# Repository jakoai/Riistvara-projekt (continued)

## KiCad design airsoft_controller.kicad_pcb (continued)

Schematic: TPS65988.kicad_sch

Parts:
C88, C90, C97: 4.7uF; C_0603_1608Metric_Pad1.08x0.95mm_HandSolder
C89, C98: 10uF; C_0805_2012Metric_Pad1.18x1.45mm_HandSolder
C91, C94, C100, C106: 1uF; C_0603_1608Metric_Pad1.08x0.95mm_HandSolder
C92, C93, C95, C96: 220pF; C_0603_1608Metric_Pad1.08x0.95mm_HandSolder
C99, C105: 0.1uF; C_0603_1608Metric_Pad1.08x0.95mm_HandSolder
C101, C102, C103, C104, C107, C108, C109, C110: 10nF; C_0603_1608Metric_Pad1.08x0.95mm_HandSolder
J8, J10: USB_C_Receptacle; USB-C-2305018-2
J9, J12: Conn_01x01; PinSocket_1x01_P2.54mm_Vertical
J11: Conn_01x05; PinSocket_1x05_P2.54mm_Vertical
R32, R33: 100k; R_0603_1608Metric_Pad0.98x0.95mm_HandSolder
R34: R_select 10k; 0603-R-select
R35: 0R 1%; R_0603_1608Metric_Pad0.98x0.95mm_HandSolder
R36: R 1%; R_0603_1608Metric_Pad0.98x0.95mm_HandSolder
R37: 150k 1%; R_0603_1608Metric_Pad0.98x0.95mm_HandSolder
R38: 180k 1%; R_0603_1608Metric_Pad0.98x0.95mm_HandSolder
RN4: 10k; R_Array_SIP9
TP4, TP5, TP6, TP7, TP8, TP9: TestPoint; TestPoint_Pad_D1.5mm
U13, U15: TPD6S300A; WQFN-20-1EP_3x3mm_P0.4mm_EP1.7x1.7mm
U14: TPS65988; VQFN-56-3EP

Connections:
+5V: C88.2, C90.2, U14.25 (PP1_CABLE), U14.46 (PP2_CABLE); also elsewhere on the board
/BATTERY_BALANCE_EN: RN4.5 (R4), U14.17 (GPIO1); also elsewhere on the board
/BATTERY_MGMT_OTG: RN4.4 (R3), U14.18 (GPIO2); also elsewhere on the board
/CP2102_USB_D+: J10.A6 (D+), J10.B6 (D+), U14.54 (C2_USB_P), U15.20 (D1); also elsewhere on the board
/CP2102_USB_D-: J10.A7 (D-), J10.B7 (D-), U14.55 (C2_USB_N), U15.19 (D2); also elsewhere on the board
/MCU_I2C_SCL: U14.27 (I2C1_SCL); also elsewhere on the board
/MCU_I2C_SDA: U14.28 (I2C1_SDA); also elsewhere on the board
/MCU_USB_D+: J8.A6 (D+), J8.B6 (D+), U13.20 (D1), U14.50 (C1_USB_P); also elsewhere on the board
/MCU_USB_D-: J8.A7 (D-), J8.B7 (D-), U13.19 (D2), U14.53 (C1_USB_N); also elsewhere on the board
/USB-C power controller/GPIO0: U14.16 (GPIO0); also elsewhere on the board
/USB-C power controller/GPIO3/HPD1: U14.30 (GPIO3/HPD1); also elsewhere on the board
/USB-C power controller/GPIO4/HPD2: U14.31 (GPIO4/HPD2); also elsewhere on the board
/USB-C power controller/TPS_ADCIN1: R37.1, R38.1, U14.6 (ADCIN1)
/USB-C power controller/TPS_ADCIN2: R35.1, R36.1, U14.10 (ADCIN2)
/USB-C power controller/TPS_LDO_1V8: C97.2, U14.35 (LDO_1V8)
/USB-C power controller/TPS_LDO_3V3: C89.2, R34.2, R36.2, R38.2, U14.9 (LDO_3V3); also elsewhere on the board
/USB-C power controller/TPS_PP_EXT1: U14.48 (GPIO16/PP_EXT1); also elsewhere on the board
/USB-C power controller/TPS_PP_EXT2: U14.49 (GPIO17/PP_EXT2); also elsewhere on the board
/USB-C power controller/TPS_SPI_POCI: J11.1, R34.3, U14.36 (SPI_POCI)
/USB-C power controller/USB1_CC1: C92.1, U13.7 (RPD_G1), U13.12 (CC1), U14.24 (C1_CC1)
/USB-C power controller/USB1_CC2: C93.1, U13.6 (RPD_G2), U13.11 (CC2), U14.26 (C1_CC2)
/USB-C power controller/USB1_C_CC1: J8.A5 (CC1), U13.4 (C_CC1)
/USB-C power controller/USB1_C_CC2: J8.B5 (CC2), U13.5 (C_CC2)
/USB-C power controller/USB1_C_SBU1: J8.A8 (SBU1), U13.1 (C_SBU1)
/USB-C power controller/USB1_C_SBU2: J8.B8 (SBU2), U13.2 (C_SBU2)
/USB-C power controller/USB1_SOURCE: U14.11 (PP_HV1), U14.12 (PP_HV1); also elsewhere on the board
/USB-C power controller/USB1_SOURCE_EN: RN4.6 (R5), U14.40 (GPIO12); also elsewhere on the board
/USB-C power controller/USB1_SOURCE_VOLTAGE_PWM: RN4.8 (R7), U14.42 (GPIO14/PWM); also elsewhere on the board
/USB-C power controller/USB1_VBUS: C91.1, C101.1, C102.1, C103.1, C104.1, J8.A4 (VBUS), J8.A9 (VBUS), J8.B4 (VBUS), J8.B9 (VBUS), U14.13 (VBUS1), U14.14 (VBUS1); also elsewhere on the board
/USB-C power controller/USB2_CC1: C95.1, U14.45 (C2_CC1), U15.7 (RPD_G1), U15.12 (CC1)
/USB-C power controller/USB2_CC2: C96.1, U14.47 (C2_CC2), U15.6 (RPD_G2), U15.11 (CC2)
/USB-C power controller/USB2_C_CC1: J10.A5 (CC1), U15.4 (C_CC1)
/USB-C power controller/USB2_C_CC2: J10.B5 (CC2), U15.5 (C_CC2)
/USB-C power controller/USB2_C_SBU1: J10.A8 (SBU1), U15.1 (C_SBU1)
/USB-C power controller/USB2_C_SBU2: J10.B8 (SBU2), U15.2 (C_SBU2)
/USB-C power controller/USB2_SOURCE: U14.1 (PP_HV2), U14.2 (PP_HV2); also elsewhere on the board
/USB-C power controller/USB2_SOURCE_EN: RN4.7 (R6), U14.41 (GPIO13); also elsewhere on the board
/USB-C power controller/USB2_SOURCE_VOLTAGE_PWM: RN4.9 (R8), U14.43 (GPIO15/PWM); also elsewhere on the board
/USB-C power controller/USB2_VBUS: C94.1, C107.1, C108.1, C109.1, C110.1, J10.A4 (VBUS), J10.A9 (VBUS), J10.B4 (VBUS), J10.B9 (VBUS), U14.3 (VBUS2), U14.4 (VBUS2); also elsewhere on the board
/USB_PD_CNTR_RESET: U14.44 (HRESET); also elsewhere on the board
/USB_PD_I2C1_IRQ: U14.29 (~I2C1_IRQ); also elsewhere on the board
GND: C88.1, C89.1, C90.1, C91.2, C92.2, C93.2, C94.2, C95.2, C96.2, C97.1, C98.1, C99.1, C100.1, C101.2, C102.2, C103.2, C104.2, C105.1, C106.1, C107.2, C108.2, C109.2, C110.2, J8.A1 (GND), J8.A12 (GND), J8.B1 (GND), J8.B12 (GND), J8.S1 (SHIELD), J10.A1 (GND), J10.A12 (GND), J10.B1 (GND), J10.B12 (GND), J10.S1 (SHIELD), J11.5, R34.1, R35.2, R37.2, RN4.1 (common), U13.8 (GND), U13.13 (GND), U13.18 (GND), U13.21 (PAD), U14.20 (GND), U14.51 (GND), U14.59 (PPAD), U15.8 (GND), U15.13 (GND), U15.18 (GND), U15.21 (PAD); also elsewhere on the board
unnamed: C99.2, U13.3 (VBIAS)
unnamed: C105.2, U15.3 (VBIAS)
unnamed: J9.1, R32.1, U13.9 (~FLT)
unnamed: J11.2, U14.37 (SPI_PICO)
unnamed: J11.3, U14.38 (SPI_CLK)
unnamed: J11.4, U14.39 (~SPI_CS)
unnamed: J12.1, R33.1, U15.9 (~FLT)
unnamed: U14.8 (DRAIN1), U14.15 (DRAIN1), U14.19 (DRAIN1), U14.58 (DRAIN1)
unnamed: TP7.1, U14.21 (I2C3_SCL)
unnamed: TP8.1, U14.22 (I2C3_SDA)
unnamed: TP9.1, U14.23 (~I2C3_IRQ)
unnamed: TP4.1, U14.32 (I2C2_SCL)
unnamed: TP5.1, U14.33 (I2C2_SDA)
unnamed: TP6.1, U14.34 (~I2C2_IRQ)
unnamed: U14.7 (DRAIN2), U14.52 (DRAIN2), U14.56 (DRAIN2), U14.57 (DRAIN2)

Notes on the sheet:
THUNDERBOLT CTRL
TSP65988 SPI FLASH
USB-PD controller
| SPI_POCI | R_left | R_right | DEAD_BAT_MODE | DEVICE_CONFIG | ------------------------------------------------------- | high | 50k | 470k | NoResponse | Safe config | | high | 100k | 300k | WaitFor3V3Int | Safe config | | high | 100k | 200k | ECWaitInt | Infinite wait | | high | 150k | 180k | Wai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
I2C MASTER
| R_left | R_right | I2C1_C1 | I2C1_C2 | I2C2_C1 | I2C2_C2 | ----------------------------------------------------------- | 0R | NC | 0x20 | 0x24 | 0x38 | 0x3F | | 100k | 220k | 0x21 | 0x25 | 0x3F | 0x38 | | 100k | 100k | 0x22 | 0x26 | 0x4F | 0x48 | | NC | 0R | 0x23 | 0x27 | 0x48 | 0x4F |
USB-C 2
SYSTEM CTRL
ADCIN2 CONFIG
ADCIN1 CONFIG
USB-C 1

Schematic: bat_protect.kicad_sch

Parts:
BT1: Battery 2S; BAT_CONN_5mm_pitch
C111, C112, C113: 0.1uF; C_0603_1608Metric_Pad1.08x0.95mm_HandSolder
C114: 0.33uF; C_0603_1608Metric_Pad1.08x0.95mm_HandSolder
C115, C116: 10uF; C_1206_3216Metric_Pad1.33x1.80mm_HandSolder
F1: Fuse; fuse_clip_5x20-33mm
JP1: Battery_balance_connector_2S; JST_XH_3P-Horizontal
Q6, Q7, Q8: Q_NMOS_DGS; SOT-23
R39: 160R; R_0603_1608Metric_Pad0.98x0.95mm_HandSolder
R40, R43: 100R; R_Box_L13.0mm_W4.0mm_P9.00mm
R41: 260R; R_0603_1608Metric_Pad0.98x0.95mm_HandSolder
R42: 0R; R_0603_1608Metric_Pad0.98x0.95mm_HandSolder
R44: 1k; R_0603_1608Metric_Pad0.98x0.95mm_HandSolder
U16: BQ29209DRBR; VSON-8

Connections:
+BATT: C115.2, C116.2, F1.1; also elsewhere on the board
/BATTERY_BALANCE_EN: U16.6 (~CB_EN); also elsewhere on the board
/BATTERY_FAULT: Q8.3 (D); also elsewhere on the board
/Battery manager/Battery protection/BAT_CB2: JP1.1 (+), Q6.2 (S), R39.1, R43.1
/Battery manager/Battery protection/BQ29_VC1: C111.1, C112.1, R41.2, U16.2 (VC1)
/Battery manager/Battery protection/BQ29_VC1_CB: Q6.1 (G), Q7.1 (G), R42.2, U16.3 (VC1_CB)
/Battery manager/Battery protection/BQ29_VC2: C111.2, R39.2, U16.1 (VC2)
GND: BT1.2 (-), C112.2, C113.2, C114.1, C115.1, C116.1, JP1.3 (-), Q7.3 (D), Q8.2 (S), U16.5 (GND), U16.PAD (GND); also elsewhere on the board
unnamed: BT1.1 (+), F1.2
unnamed: C113.1, R43.2, U16.7 (VDD)
unnamed: C114.2, U16.4 (CD)
unnamed: JP1.2 (C1), R40.1, R41.1
unnamed: Q6.3 (D), Q7.2 (S), R40.2, R42.1
unnamed: Q8.1 (G), R44.2
unnamed: R44.1, U16.8 (OUT)

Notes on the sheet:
ext balance 0R if no ext R >2k if ext
I_{bal} = V_{CELL}/R_{CB}
int balance I_{CB1}= V_{C1} ~{R_{VC1}+R_{VC1_CB}} I_{CB2}= V_{C2}-V_{C1} ~{R_{VC2}+R_{VC1_CB}+R_{VDD}} Supports max 15mA balance

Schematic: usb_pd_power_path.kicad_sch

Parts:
C133, C134: 1uF; C_0603_1608Metric_Pad1.08x0.95mm_HandSolder
C135, C136, C137, C138, C139, C140, C143, C144, C149, C151, C159, C162: 0.1uF; C_0603_1608Metric_Pad1.08x0.95mm_HandSolder
C141, C142, C160, C163: 10uF; C_0805_2012Metric_Pad1.18x1.45mm_HandSolder
C145, C146: 22nF; C_0603_1608Metric_Pad1.08x0.95mm_HandSolder
C147, C148: C; C_0603_1608Metric_Pad1.08x0.95mm_HandSolder
C150, C152: 15pF; C_0603_1608Metric_Pad1.08x0.95mm_HandSolder
C153, C154, C155, C156, C157, C158, C161, C164: 22uF; CP_Elec_5x5.3
L7, L8: 1uH; Inductor_8030
Q9, Q10: Q_Dual_PMOS; SO-8_3.9x4.9mm_P1.27mm
Q11, Q12, Q13, Q14, Q15, Q16: Q_NMOS_DGS; SOT-23
R45, R47, R49, R51: 60k; R_0603_1608Metric_Pad0.98x0.95mm_HandSolder
R46, R48, R50, R52, R55, R56, R59, R60: 10k; R_0603_1608Metric_Pad0.98x0.95mm_HandSolder
R53, R54: 576k; R_0603_1608Metric_Pad0.98x0.95mm_HandSolder
R57, R58, R63, R64, R67, R69: 100k; R_0603_1608Metric_Pad0.98x0.95mm_HandSolder
R61, R62: 1k; R_0603_1608Metric_Pad0.98x0.95mm_HandSolder
R65, R66: R; R_0603_1608Metric_Pad0.98x0.95mm_HandSolder
R68, R70: 30k; R_0603_1608Metric_Pad0.98x0.95mm_HandSolder
R71, R73: 10R; R_0603_1608Metric_Pad0.98x0.95mm_HandSolder
R72, R74: 20k; R_0603_1608Metric_Pad0.98x0.95mm_HandSolder
R75, R77: 20k 1%; R_0603_1608Metric_Pad0.98x0.95mm_HandSolder
R76, R78: 604R 1%; R_0603_1608Metric_Pad0.98x0.95mm_HandSolder
U17: LM358; SOIC-8_3.9x4.9mm_P1.27mm
U18, U19: MP2229GQ-P; QFN-14

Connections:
/USB-C power controller/TPS_LDO_3V3: R55.2, R56.2, U17.8 (V+); also elsewhere on the board
/USB-C power controller/TPS_PP_EXT1: R61.1; also elsewhere on the board
/USB-C power controller/TPS_PP_EXT2: R62.1; also elsewhere on the board
/USB-C power controller/USB1_SOURCE: C151.1, C152.1, C156.1, C157.1, C158.1, L8.2, R77.1; also elsewhere on the board
/USB-C power controller/USB1_SOURCE_EN: U19.5 (EN); also elsewhere on the board
/USB-C power controller/USB1_SOURCE_VOLTAGE_PWM: Q16.1 (G); also elsewhere on the board
/USB-C power controller/USB1_VBUS: C133.1, C135.1, Q9.7 (D), Q9.8 (G); also elsewhere on the board
/USB-C power controller/USB2_SOURCE: C149.1, C150.1, C153.1, C154.1, C155.1, L7.2, R75.1; also elsewhere on the board
/USB-C power controller/USB2_SOURCE_EN: U18.5 (EN); also elsewhere on the board
/USB-C power controller/USB2_SOURCE_VOLTAGE_PWM: Q15.1 (G); also elsewhere on the board
/USB-C power controller/USB2_VBUS: C134.1, C136.1, Q10.7 (D), Q10.8 (G); also elsewhere on the board
/USB-C power controller/USB Power paths/MP_1_LDO_5V: C144.2, R69.2, U19.10 (VCC)
/USB-C power controller/USB Power paths/MP_2_LDO_5V: C143.2, R67.2, U18.10 (VCC)
GND: C133.2, C134.2, C141.2, C142.2, C143.1, C144.1, C145.2, C146.2, C147.2, C148.2, C153.2, C154.2, C155.2, C156.2, C157.2, C158.2, C159.2, C160.2, C161.2, C162.2, C163.2, C164.2, Q11.2 (S), Q12.2 (S), Q13.2 (S), Q14.2 (S), Q15.2 (S), Q16.2 (S), R46.1, R48.1, R50.1, R52.1, R63.2, R64.2, R65.1, R66.1, R68.1, R70.1, U17.4 (V-), U18.1 (GND), U18.12 (GND), U18.13 (GND), U18.14 (GND), U19.1 (GND), U19.12 (GND), U19.13 (GND), U19.14 (GND); also elsewhere on the board
unnamed: C135.2, C137.2, C139.2, Q9.2 (G), Q9.4 (G), R57.2, R59.1
unnamed: C136.2, C138.2, C140.2, Q10.2 (G), Q10.4 (G), R58.2, R60.1
unnamed: C137.1, Q9.1 (S), Q9.3 (S), R49.1, R57.1
unnamed: C138.1, Q10.1 (S), Q10.3 (S), R51.1, R58.1
unnamed: C145.1, U18.8 (SS)
unnamed: C146.1, U19.8 (SS)
unnamed: C147.1, C150.2, R72.1, R75.2, R76.1
unnamed: C148.1, C152.2, R74.1, R77.2, R78.1
unnamed: C149.2, R71.2
unnamed: C151.2, R73.2
unnamed: L7.1, U18.2 (SW), U18.4 (SW)
unnamed: L8.1, U19.2 (SW), U19.4 (SW)
unnamed: Q11.1 (G), R53.1, R55.1, U17.1
unnamed: Q11.3 (D), Q13.1 (G), R61.2, R63.1
unnamed: Q12.1 (G), R54.1, R56.1, U17.7
unnamed: Q12.3 (D), Q14.1 (G), R62.2, R64.1
unnamed: Q13.3 (D), R59.2
unnamed: Q14.3 (D), R60.2
unnamed: Q15.3 (D), R76.2
unnamed: Q16.3 (D), R78.2
unnamed: R45.2, R46.2, U17.3 (+)
unnamed: R47.2, R48.2, U17.5 (+)
unnamed: R49.2, R50.2, R53.2, U17.2 (-)
unnamed: R51.2, R52.2, R54.2, U17.6 (-)
unnamed: R65.2, R67.1, U18.6 (LPM)
unnamed: R66.2, R69.1, U19.6 (LPM)
unnamed: R68.2, U18.9 (FREQ/SYNC)
unnamed: R70.2, U19.9 (FREQ/SYNC)
unnamed: R71.1, U18.11 (BST)
unnamed: R72.2, U18.7 (FB)
unnamed: R73.1, U19.11 (BST)
unnamed: R74.2, U19.7 (FB)
SYS VBUS: C139.1, C140.1, C141.1, C142.1, C159.1, C160.1, C161.1, C162.1, C163.1, C164.1, Q9.5 (D), Q9.6 (G), Q10.5 (D), Q10.6 (G), R45.1, R47.1, U18.3 (IN), U18.15 (IN), U19.3 (IN), U19.15 (IN); also elsewhere on the board

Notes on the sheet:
F_{s}(kHz) = 16000 ~{(R(kHz)+2.3)}
USB1 VBUS to SYS VBUS
Recommended: Reverse current protection. Enables Ext and Int ćontrol at the same time
SYS VBUS to USB2
USB2 VBUS to SYS VBUS
SYS VBUS to USB1

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
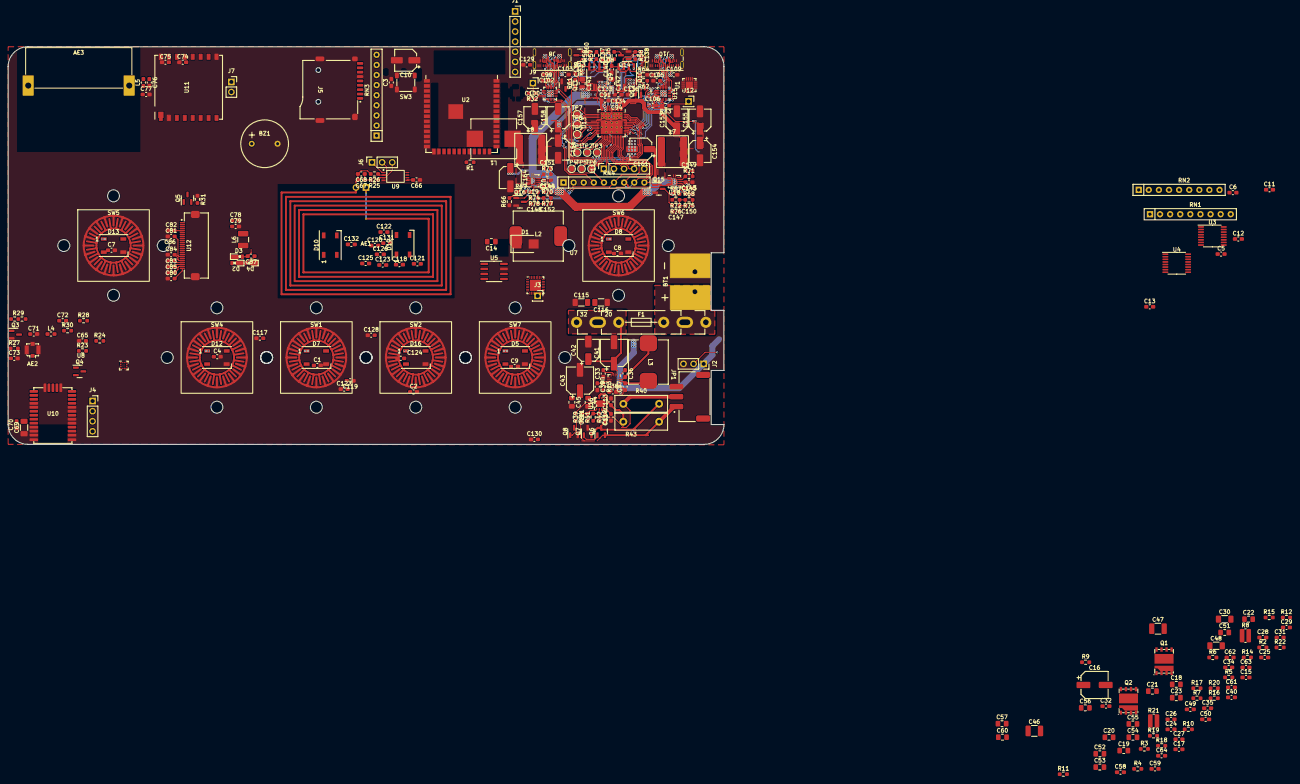
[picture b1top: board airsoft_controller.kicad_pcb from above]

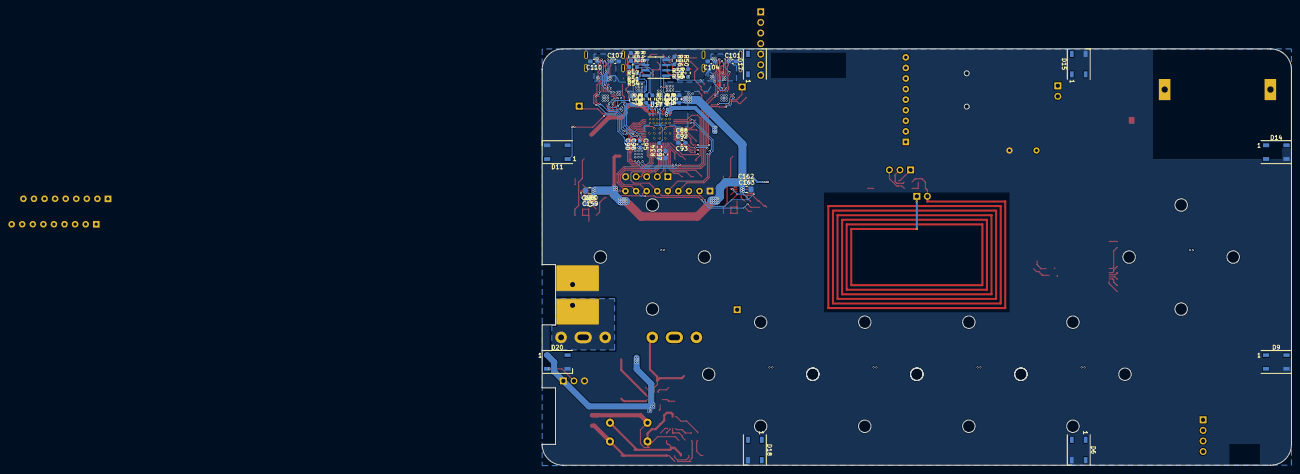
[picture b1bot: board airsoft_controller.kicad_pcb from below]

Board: 2 copper layers, 180.0 x 100.0 mm, 344 parts (44 on the bottom side), 253 nets.

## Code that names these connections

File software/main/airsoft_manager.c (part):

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    ESP_LOGI(TAG, "USB initialization DONE");

    gpio_num_t shift_in_out_latch = GPIO_NUM_45;
    gpio_num_t shift_out_clk = GPIO_NUM_46;
    gpio_num_t shift_out_data = GPIO_NUM_3;
    gpio_num_t shift_out_clr = GPIO_NUM_16;
    gpio_set_direction(shift_out_clr, GPIO_MODE_OUTPUT);
    gpio_set_level(shift_out_clr, 0);
    gpio_set_direction(shift_in_out_latch, GPIO_MODE_OUTPUT);
    gpio_set_direction(shift_out_clk, GPIO_MODE_OUTPUT);
    gpio_set_direction(shift_out_data, GPIO_MODE_OUTPUT);
    gpio_set_direction(shift_out_clr, GPIO_MODE_OUTPUT);
    gpio_set_level(shift_out_clk, 0);
    gpio_set_level(shift_out_data, 0);
    gpio_set_level(shift_out_clr, 1);
    uint8_t shift_out_state = 0b10000000; //enable 5V supply
    for (int8_t i = 7; i >= 0; i--){
        gpio_set_level(shift_out_data, shift_out_state&(1<<i));
        gpio_set_level(shift_out_clk, 1);
        gpio_set_level(shift_out_clk, 0);
    }
    gpio_set_level(shift_in_out_latch, 1);
    gpio_set_level(shift_in_out_latch, 0);
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
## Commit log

2022-10-03 initial commit, IMU ESP and USB-PD symbols
2022-10-03 added git ignore
2022-10-03 removed temp files
2022-10-05 added lora, gps, nfc schematics
2022-10-08 Added display, update lora sym, updated usb-pd schematic, connected sd, added external buttons
2022-10-11 Added new lora, added rgb leds, updated TSP65988 schematic, added bat to 3v3, added battery balancer
2022-10-17 added digi-pote symbol, added USB_source voltage regulators
2022-10-19 added audio ref schematic, added bat to 5V, added shift register, connected devices with other periferals
2022-10-19 fixes
2022-10-19 added adcin2 config description, fixed some rule check errors
2022-10-20 added external connectors
2022-10-21 minor optimized pinassignement, added capacitors, added connectors
2022-10-22 PI LC lowpass filter, added CP2012 reset, added connectors
2022-10-22 datasheet checkout, added couple of capacitors for usb-c, groupd some scheatics
2022-10-25 added nfc antenna components, added most of footprints
2022-10-25 added inductors to component list
2022-11-04 schematic creation
2022-11-06 edited usb pcb part
2022-11-07 usb power source added, need to reassemble to 4-layers
2022-11-12 done first iteration of pcb routing, slikscreen still broken
2022-11-12 removed silkscreen warning markers
2022-11-21 mounting holes, fixes silkscreen
2022-11-21 added more text
2022-11-23 copied own LED footprint, modified silkscreen, minor visual changes in schematics
2022-11-24 minor changes
2022-11-24 added more ground vias for specific components, fixed battery current schunt measurement trace start point, removed small groud plane next to LoRa antenna
2022-11-26 final pcb check and minor fixes
2023-01-03 minor setting changes in schematics, added test software container
